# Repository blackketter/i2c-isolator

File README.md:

I2C Isolator Board.  

Uses TI iso1540 IC or equivalent.

Includes Sparkfun qwiic connectors (and headers).

Designed in kicad.

Available at [oshpark](https://oshpark.com/shared_projects/gqwzSxCl)

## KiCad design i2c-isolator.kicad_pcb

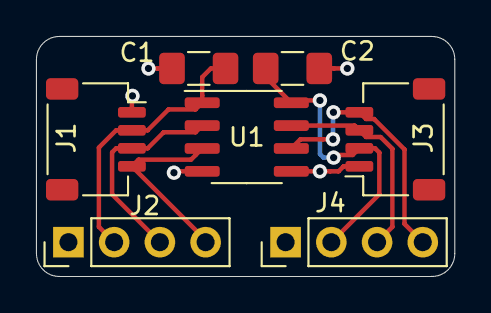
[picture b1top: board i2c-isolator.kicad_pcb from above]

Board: 2 copper layers, 23.2 x 13.3 mm, 7 parts (0 on the bottom side), 8 nets.

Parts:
C1, C2: 0.1u; C_1206_3216Metric_Pad1.42x1.75mm_HandSolder
J1, J3: qwiik; JST_SH_SM04B-SRSS-TB_1x04-1MP_P1.00mm_Horizontal
J2, J4: header; PinHeader_1x04_P2.54mm_Vertical
U1: ISO1540; SOIC-8_3.9x4.9mm_P1.27mm

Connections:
/GND1: C1.1, J1.1, J2.1, U1.4
/GND2: C2.1, J3.1, J4.1, U1.5
/SCL1: J1.4, J2.4, U1.3
/SCL2: J3.4, J4.4, U1.6
/SDA1: J1.3, J2.3, U1.2
/SDA2: J3.3, J4.3, U1.7
/VCC1: C1.2, J1.2, J2.2, U1.1
/VCC2: C2.2, J3.2, J4.2, U1.8

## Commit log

2019-09-04 First version, PCB ordered
2019-09-04 Add README and schematic PDF
2019-09-05 Add images
2019-09-05 Add link to oshpark
